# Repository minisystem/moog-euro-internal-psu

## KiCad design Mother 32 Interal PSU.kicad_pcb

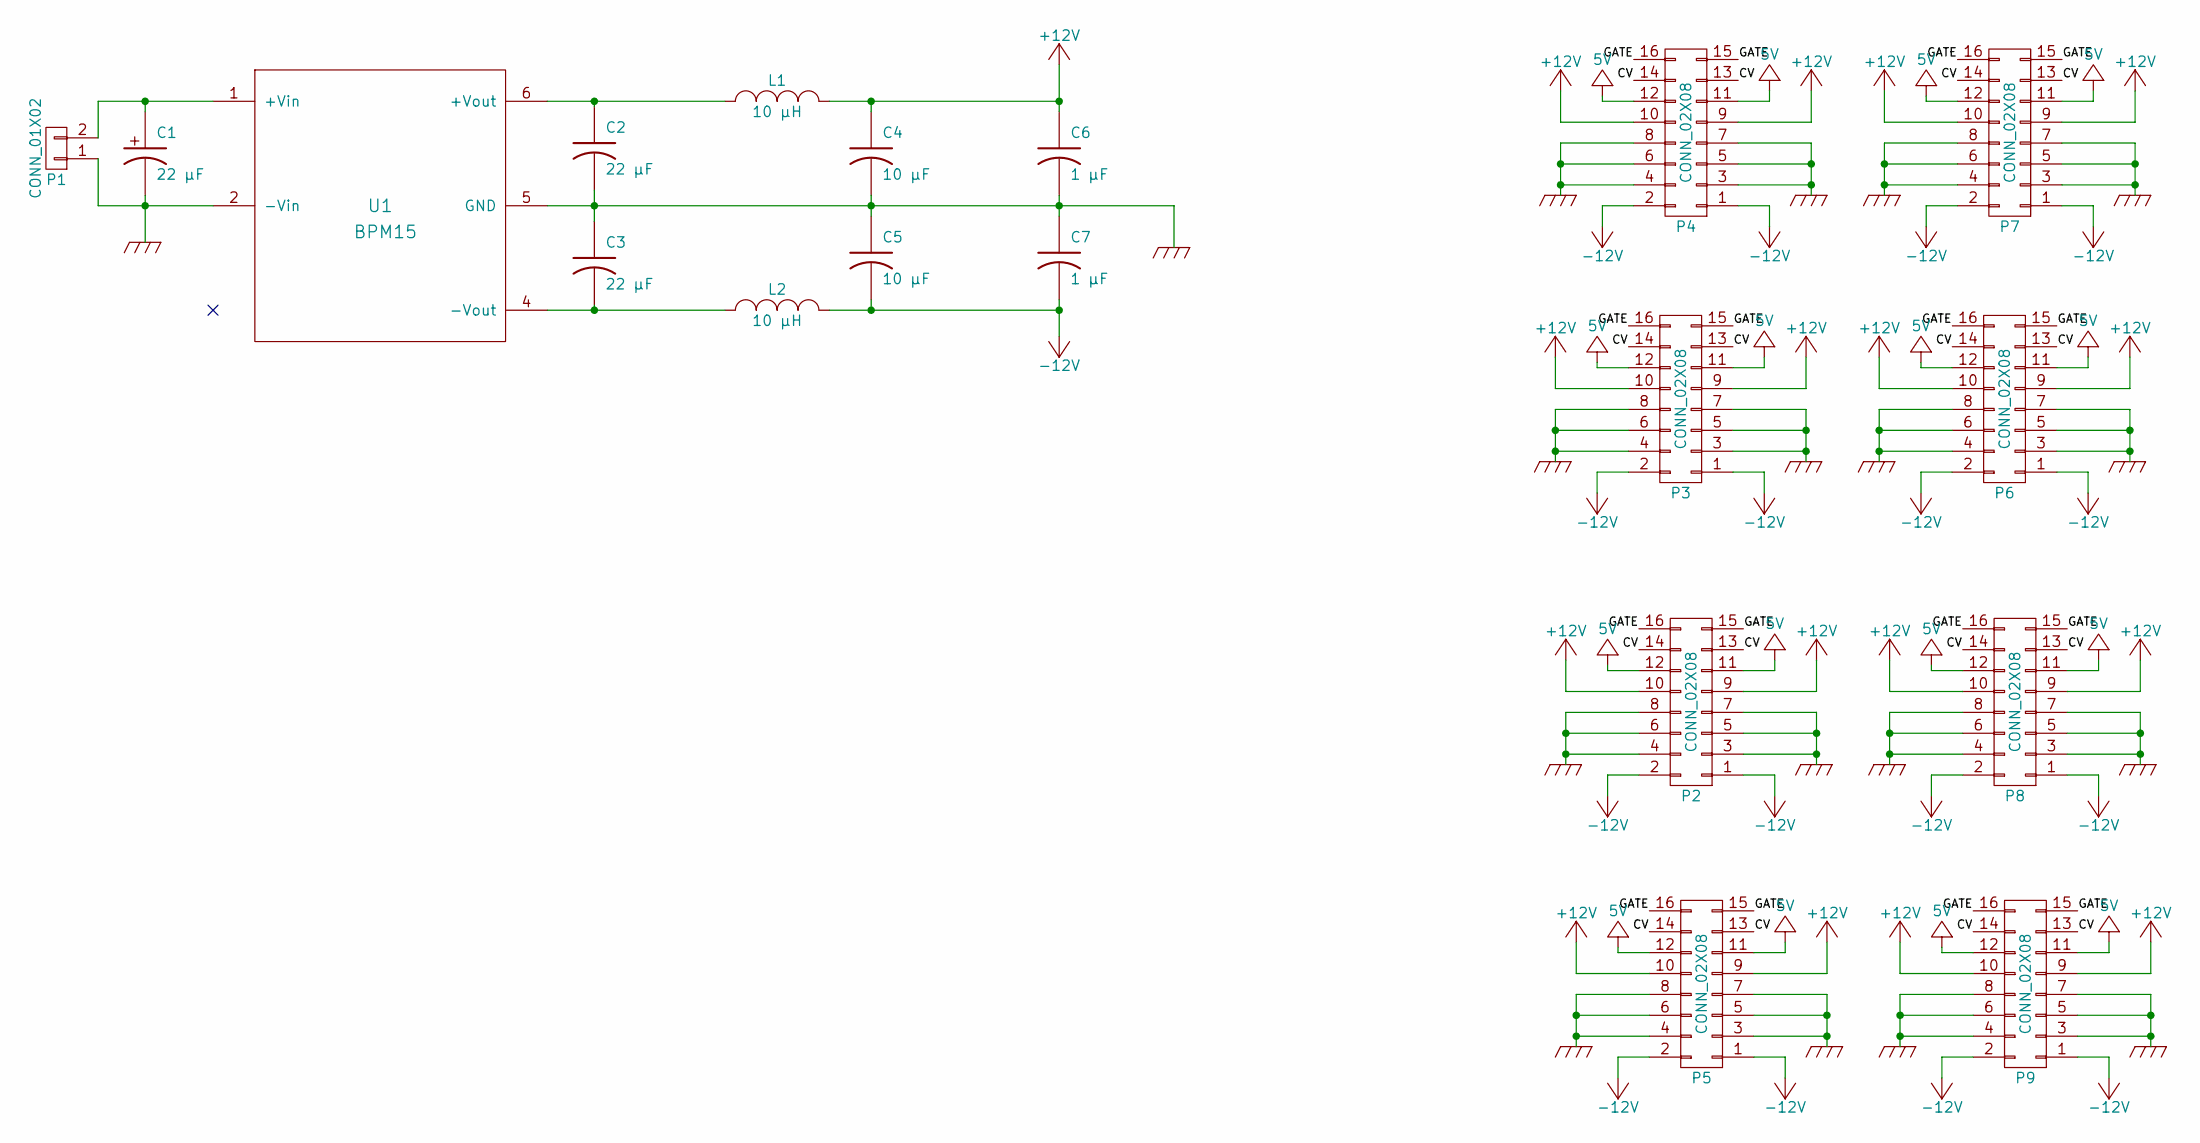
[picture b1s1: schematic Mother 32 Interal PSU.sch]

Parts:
C1: 22 μF; c_elec_5x5.3
C2, C3: 22 μF; C_1210_HandSoldering
C4, C5: 10 μF; C_1206
C6, C7: 1 μF; C_0805
L1, L2: 10 μH; L_Taiyo-Yuden_NR-60xx_HandSoldering
P1: CONN_01X02; kk156_26-60-4020
P2, P3, P4, P5, P6, P7, P8, P9: CONN_02X08; Pin_Header_Straight_2x08_Pitch2.54mm
U1: BPM15; BMP15-DIP6

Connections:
+5V: P2.11, P2.12, P3.11, P3.12, P4.11, P4.12, P5.11, P5.12, P6.11, P6.12, P7.11, P7.12, P8.11, P8.12, P9.11, P9.12
+12V: C4.1, C6.1, L1.2, P2.9, P2.10, P3.9, P3.10, P4.9, P4.10, P5.9, P5.10, P6.9, P6.10, P7.9, P7.10, P8.9, P8.10, P9.9, P9.10
-12V: C5.2, C7.2, L2.2, P2.1, P2.2, P3.1, P3.2, P4.1, P4.2, P5.1, P5.2, P6.1, P6.2, P7.1, P7.2, P8.1, P8.2, P9.1, P9.2
/CV: P2.13, P2.14, P3.13, P3.14, P4.13, P4.14, P5.13, P5.14, P6.13, P6.14, P7.13, P7.14, P8.13, P8.14, P9.13, P9.14
/GATE: P2.15, P2.16, P3.15, P3.16, P4.15, P4.16, P5.15, P5.16, P6.15, P6.16, P7.15, P7.16, P8.15, P8.16, P9.15, P9.16
GND: C1.2 (-), C2.2, C3.1, C4.2, C5.1, C6.2, C7.1, P1.1, P2.3, P2.4, P2.5, P2.6, P2.7, P2.8, P3.3, P3.4, P3.5, P3.6, P3.7, P3.8, P4.3, P4.4, P4.5, P4.6, P4.7, P4.8, P5.3, P5.4, P5.5, P5.6, P5.7, P5.8, P6.3, P6.4, P6.5, P6.6, P6.7, P6.8, P7.3, P7.4, P7.5, P7.6, P7.7, P7.8, P8.3, P8.4, P8.5, P8.6, P8.7, P8.8, P9.3, P9.4, P9.5, P9.6, P9.7, P9.8, U1.2 (-Vin), U1.5 (GND)
unnamed: C1.1 (+), P1.2, U1.1 (+Vin)
unnamed: C2.1, L1.1, U1.6 (+Vout)
unnamed: C3.2, L2.1, U1.4 (-Vout)

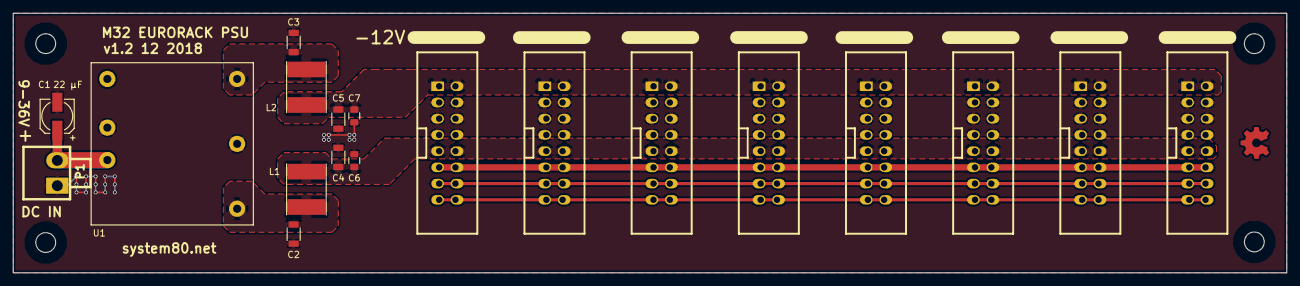
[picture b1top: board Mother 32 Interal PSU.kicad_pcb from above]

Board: 4 copper layers, 199.4 x 40.6 mm, 23 parts (0 on the bottom side), 9 nets.

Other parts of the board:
HOLE-M3, HOLE-M3#2, HOLE-M3#3, HOLE-M3#4: VAL**; HOLE-M3

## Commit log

2017-01-02 updated silkscreen
2018-05-22 updated ground planes and power traces, added CV/GATE connections
2018-05-22 generated gerbers for new version, 1.1
2018-12-10 first commit with LDOs but these things will just get too damn hot, so will now revert to just LC filter on output
2018-12-10 added LC filter to outputs
2018-12-10 LC filter added to output
2019-10-07 4 layer
